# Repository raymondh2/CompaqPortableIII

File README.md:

# CompaqPortableIII

Current PCB Memory Expansion board layout is untested. The backplane for the expansion cards is tested and working.

Recreation of U10 Part Number 107393-001 working as expected so far. Recreation of U20 Part Number 107392-001 is untested.

The mainboard schematics are not verfied or complete.

## Other Projects
Replacement Battery Module by Sergey Kiselev [GitHub](https://github.com/skiselev/compaq-portable-iii-battery)

## License
This work is licensed under the CERN Open Hardware License v2 Strongly Reciprocal.
See [here](cern_ohl_s_v2_user_guide.txt).

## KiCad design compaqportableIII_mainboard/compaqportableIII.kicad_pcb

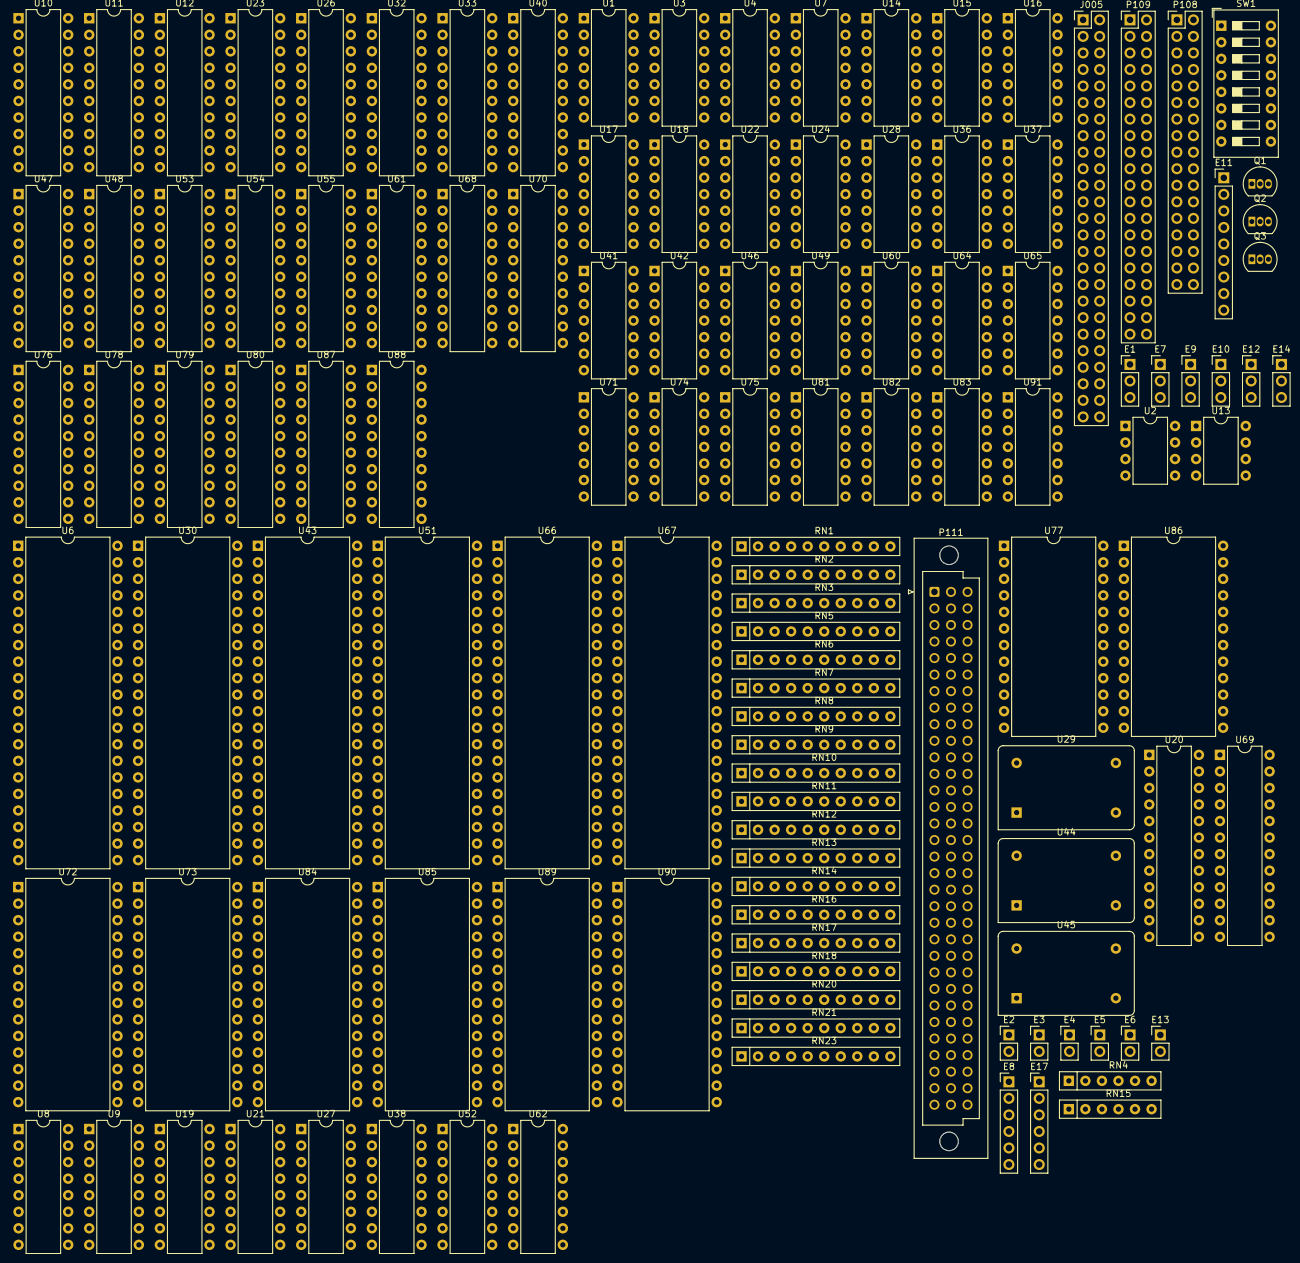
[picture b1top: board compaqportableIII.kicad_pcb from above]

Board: 2 copper layers, 123 parts (0 on the bottom side), 421 nets, no tracks yet.

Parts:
E1, E7, E9, E10, E12, E14: Conn_01x03; PinHeader_1x03_P2.54mm_Vertical
E2, E3, E4, E5, E6, E13: Conn_01x02; PinHeader_1x02_P2.54mm_Vertical
E8, E17: Conn_01x06; PinHeader_1x06_P2.54mm_Vertical
E11: Conn_01x09; PinHeader_1x09_P2.54mm_Vertical
J005: Conn_02x25_Odd_Even; PinHeader_2x25_P2.54mm_Vertical
P108: Conn_02x17_Odd_Even; PinHeader_2x17_P2.54mm_Vertical
P109: Conn_02x20_Odd_Even; PinHeader_2x20_P2.54mm_Vertical
P111: DIN41612_96abc; DIN41612_R_3x32_Male_Vertical_THT
Q1: TL431C; TO-92_Inline
Q2, Q3: PN2222A; TO-92_Inline
RN1: 1K; R_Array_SIP10
RN2: 2K; R_Array_SIP10
RN3, RN5, RN6, RN8, RN9, RN10, RN11, RN12, RN13, RN14, RN20, RN21, RN23: 8K2; R_Array_SIP10
RN4: 300R; R_Array_SIP6
RN7: 180; R_Array_SIP10
RN15: 100R; R_Array_SIP6
RN16, RN17, RN18: 33R; R_Array_SIP10
SW1: SW_DIP_x08; SW_DIP_SPSTx08_Slide_9.78x22.5mm_W7.62mm_P2.54mm
U1, U4: 7406N; DIP-14_W7.62mm
U2: SN75477; DIP-8_W7.62mm
U3: MC4024; DIP-14_W7.62mm
U6: D765; DIP-40_W15.24mm
U7: 74ALS00; DIP-14_W7.62mm
U8: 74LS112; DIP-16_W7.62mm
U9: MC3487N; DIP-16_W7.62mm
U10: PAL16L8; DIP-20_W7.62mm
U11, U23, U26: 74LS245; DIP-20_W7.62mm
U12: 74LS244; DIP-20_W7.62mm
U13: μA741CP; DIP-8_W7.62mm
U14: 74LS14; DIP-14_W7.62mm
U15: 74LS08; DIP-14_W7.62mm
U16, U91: 74ALS74; DIP-14_W7.62mm
U17: 74F08; DIP-14_W7.62mm
U18, U24, U37: 74LS125; DIP-14_W7.62mm
U19, U52: 74ALS138; DIP-16_W7.62mm
U20: PAL20L8; DIP-24_W7.62mm
U21, U27: MB8264A; DIP-16_W7.62mm
U22, U64: 74ALS04; DIP-14_W7.62mm
U28: 74LS05; DIP-14_W7.62mm
U29: F5C-S7; Oscillator_DIP-14
U30: 16450; DIP-40_W15.24mm
U32, U68, U78: 74F245; DIP-20_W7.62mm
U33, U48: 74ALS244; DIP-20_W7.62mm
U36, U41: 74F00; DIP-14_W7.62mm
U38, U62: 74LS367; DIP-16_W7.62mm
U40, U47, U70, U79, U80: 74ALS245; DIP-20_W7.62mm
U42: 74LS09; DIP-14_W7.62mm
U43: 80287; DIP-40_W15.24mm
U44: 1.843200 MHz; Oscillator_DIP-14
U45: 48 MHz; Oscillator_DIP-14
U46, U60: 74F32; DIP-14_W7.62mm
U49: 74F10; DIP-14_W7.62mm
U51: 8742; DIP-40_W15.24mm
U53: 74F257; DIP-20_W7.62mm
U54, U55, U61: 74F244; DIP-20_W7.62mm
U65: 74ALS27; DIP-14_W7.62mm
U66, U67: 8237; DIP-40_W15.24mm
U69: 74LS646; DIP-24_W7.62mm
U71, U81: 74LS280; DIP-14_W7.62mm
U72, U73, U89, U90: 27C256; DIP-28_W15.24mm
U74, U75: MC1489; DIP-14_W7.62mm
U76: 74LS374; DIP-20_W7.62mm
U77: MC146818A; DIP-24_W15.24mm
U82: MC1488; DIP-14_W7.62mm
U83: 4069; DIP-14_W7.62mm
U84, U85: 8259A-2; DIP-28_W15.24mm
U86: 8254; DIP-24_W15.24mm
U87, U88: 74LS373; DIP-20_W7.62mm

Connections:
+5V: E1.3, E10.1, E11.1, E11.4, E12.1, E13.1, E14.1, E17.1, E17.6, J005.1, J005.2, J005.49, J005.50, P111.a2 (Pin_c2), P111.a8 (Pin_c8), P111.c20, RN1.1 (R1), RN2.1 (R1), RN3.1 (common), RN4.1 (R1), RN5.1 (common), RN6.1 (common), RN8.1 (R1), RN9.1 (R1), RN10.1 (common), RN11.1 (R1), RN12.1 (common), RN13.1 (common), RN14.1 (common), RN20.1 (common), RN23.1 (common), U1.14 (VCC), U2.1 (S), U2.5 (Clamp), U2.8 (VCC), U6.35 (READY), U8.2 (K), U8.4 (~S), U8.10 (~S), U8.12 (K), U9.16 (VCC), U10.20 (VCC), U12.20 (VCC), U16.1 (~R), U16.10 (~S), U16.12 (D), U20.24 (VCC), U21.8 (VCC), U23.20 (VCC), U27.8 (VCC), U30.12 (CS0), U30.13 (CS1), U30.40 (VCC), U32.20 (VCC), U38.14 (I6), U38.16 (VCC), U43.9 (VCC), U43.39 (CKM), U47.20 (VCC), U48.20 (VCC), U51.25 (PROG), U51.26 (Vpp/VDD), U51.40 (VCC), U53.16 (VCC), U54.20 (VCC), U55.20 (VCC), U62.16 (VCC), U66.5 (PIN5), U66.31 (Vcc), U67.5 (PIN5), U67.31 (Vcc), U68.20 (VCC), U69.24 (VCC), U70.20 (VCC), U71.14 (VCC), U72.1 (VPP), U72.28 (VCC), U73.1 (VPP), U73.28 (VCC), U76.20 (VCC), U78.20 (VCC), U79.20 (VCC), U81.14 (VCC), U82.9, U82.13, U84.16 (~SP/~EN), U84.28 (VCC), U85.28 (VCC), U86.11 (G0), U86.14 (G1), U86.24 (VCC), U88.20 (VCC), U89.1 (VPP), U89.28 (VCC), U90.1 (VPP), U90.28 (VCC), U91.1 (~R), U91.4 (~S)
+12V: J005.47, P111.a6 (Pin_c6), P111.a20 (Pin_c20), U13.7 (V+)
+BATT: U77.24 (VCC), U83.14 (VDD)
-12V: J005.48, P111.b5 (Pin_c5), U13.4 (V-)
/AEN: J005.35, P111.a7 (Pin_c7), U33.16 (O1a)
/AEN2: U20.11 (I11), U33.4 (I1a), U64.2, U70.19 (CE)
/ALE: P111.b19 (Pin_c19), U33.14 (O2a)
/BA00: J005.11, P111.c21, RN20.2 (R1), U6.5 (A0), U12.13 (I1b), U20.10 (I10), U24.2, U24.6, U30.28 (A0)
/BA00_BUFF: U24.3, U24.5, U62.12 (I5), U69.22 (SBA)
/COM1: E3.1, U20.15 (IO15)
/COM2: E4.2, U20.18 (IO18)
/CPUB_A20: U47.5 (A3), U53.12 (Zc)
/CPUB_A21: U47.6 (A4), U53.9 (Zd)
/CPUB_A22: U47.7 (A5), U53.7 (Zb)
/CPUB_A23: U47.8 (A6), U53.4 (Za)
/CPU_A1: U62.4 (I2), U62.10 (I4)
/CPU_A2: U62.2 (I1), U62.6 (I3)
/CPU_A7: U37.9, U48.8 (I3a)
/CPU_A17: U33.15 (I2b), U47.2 (A0)
/CPU_A18: U33.13 (I1b), U47.3 (A1)
/CPU_A19: U33.17 (I3b), U47.4 (A2)
/CPU_A21: U53.10 (I1d), U53.11 (I0d)
/CPU_A22: U53.5 (I0b), U53.6 (I1b)
/CPU_A23: U53.2 (I0a), U53.3 (I1a)
/CPU_D0: U43.23 (D0), U69.11 (A8)
/CPU_D1: U43.22 (D1), U69.10 (A7)
/CPU_D2: U43.21 (D2), U69.9 (A6)
/CPU_D3: U43.20 (D3), U69.8 (A5)
/CPU_D4: U43.19 (D4), U69.7 (A4)
/CPU_D5: U43.18 (D5), U69.6 (A3)
/CPU_D6: U43.17 (D6), U69.5 (A2)
/CPU_D7: U43.16 (D7), U69.4 (A1)
/CPU_D8: U43.15 (D8), U79.9 (A7)
/CPU_D9: U43.14 (D9), U79.8 (A6)
/CPU_D10: U43.12 (D10), U79.7 (A5)
/CPU_D11: U43.11 (D11), U79.6 (A4)
/CPU_D12: U43.8 (D12), U79.5 (A3)
/CPU_D13: U43.7 (D13), U79.4 (A2)
/CPU_D14: U43.6 (D14), U79.3 (A1)
/CPU_D15: U43.5 (D15), U79.2 (A0)
/CPU_HDLA: U33.2 (I0a), U43.38 (HLDA), U53.15 (OE)
/CPU_~S0: RN6.3 (R2), U43.2 (~S0)
/CPU_~S1: RN6.4 (R3), U43.1 (~S1)
/Crystal_+5V: E13.2, U29.14 (VDD), U44.14 (VDD), U45.14 (VDD)
/DISKADD: E8.2, U20.23 (I23)
/DMA1_~CS: U19.15 (O0), U66.11 (~CS)
/DMA1_~EOP: U41.10, U66.36 (~EOP)
/DMA2_~CS: U19.9 (O6), U67.11 (~CS)
/DMA2_~EOP: U41.9, U67.36 (~EOP)
/DMA_CLK: RN7.6 (R3.2), U66.12 (CLK), U67.12 (CLK)
/DMA_RDY: U66.6 (READY), U67.6 (READY)
/DMA_RST: U33.8 (I3a), U33.11 (I0b), U64.11, U66.13 (RESET), U67.13 (RESET)
/DMA_~MEMR: RN11.7 (R6.2), U66.3 (~MEMR), U67.3 (~MEMR)
/DRQ0: P111.b27 (Pin_c27), RN21.2 (R1), U66.19 (DREQ0)
/DRQ1: P111.a12 (Pin_c12), RN21.3 (R2), U66.18 (DREQ1)
/DRQ2: P111.a4 (Pin_c4), RN21.4 (R3), U66.17 (DREQ2)
/DRQ3: P111.b11 (Pin_c11), RN21.5 (R4), U66.16 (DREQ3)
/DRQ5: P111.a28 (Pin_c28), RN21.7 (R6), U67.18 (DREQ1)
/DRQ6: P111.c30, RN21.8 (R7), U67.17 (DREQ2)
/DRQ7: P111.b31 (Pin_c31), RN21.9 (R8), U67.16 (DREQ3)
/DRQC: RN21.6 (R5), U66.10 (HRQ), U67.19 (DREQ0)
/DRVSB0: U1.1, U4.3
/DRVSB1: U1.5, U4.13
/DT/~R: U69.3 (DIR), U79.1 (A->B)
/EDB7: U18.3, U18.9, U18.11
/EXP_A1: J005.12, P111.b20 (Pin_c20), RN12.2 (R1), U12.15 (I2b), U20.9 (I9), U30.27 (A1), U40.2 (A0), U55.17 (I3b), U61.13 (I1b), U72.10 (A0), U73.10 (A0), U89.10 (A0), U90.10 (A0)
/EXP_A2: J005.13, P111.a19 (Pin_c19), RN12.3 (R2), U12.17 (I3b), U20.8 (I8), U30.26 (A2), U40.3 (A1), U55.15 (I2b), U61.11 (I0b), U72.9 (A1), U73.9 (A1), U89.9 (A1), U90.9 (A1)
/EXP_A3: J005.14, P111.c19, RN12.4 (R3), U20.7 (I7), U40.4 (A2), U55.13 (I1b), U72.8 (A2), U73.8 (A2), U89.8 (A2), U90.8 (A2)
/EXP_A4: J005.15, P111.b18 (Pin_c18), RN12.5 (R4), U20.6 (I6), U40.5 (A3), U55.11 (I0b), U72.7 (A3), U73.7 (A3), U89.7 (A3), U90.7 (A3)
/EXP_A5: J005.16, P111.a17 (Pin_c17), RN12.6 (R5), U19.1 (A0), U20.5 (I5), U40.6 (A4), U55.8 (I3a), U72.6 (A4), U73.6 (A4), U89.6 (A4), U90.6 (A4)
/EXP_A6: J005.17, P111.c17, RN12.7 (R6), U19.2 (A1), U20.4 (I4), U40.7 (A5), U55.6 (I2a), U72.5 (A5), U73.5 (A5), U89.5 (A5), U90.5 (A5)
/EXP_A7: J005.18, P111.b16 (Pin_c16), RN12.8 (R7), U19.3 (A2), U20.3 (I3), U40.8 (A6), U55.4 (I1a), U72.4 (A6), U73.4 (A6), U89.4 (A6), U90.4 (A6)
/EXP_A8: J005.19, P111.a15 (Pin_c15), RN12.9 (R8), U19.5 (E2), U20.2 (I2), U40.9 (A7), U55.2 (I0a), U72.3 (A7), U73.3 (A7), U89.3 (A7), U90.3 (A7)
/EXP_A9: J005.20, P111.c15, RN10.9 (R8), U19.4 (E1), U20.1 (I1), U54.17 (I3b), U61.17 (I3b), U62.13 (O6b), U72.25 (A8), U73.25 (A8), U87.5 (O1), U88.2 (O0), U89.25 (A8), U90.25 (A8)
/EXP_A10: J005.21, P111.b14 (Pin_c14), RN10.8 (R7), U54.15 (I2b), U61.15 (I2b), U72.24 (A9), U73.24 (A9), U87.19 (O7), U88.5 (O1), U89.24 (A9), U90.24 (A9)
/EXP_A11: J005.22, P111.a13 (Pin_c13), RN10.7 (R6), U54.13 (I1b), U72.21 (A10), U73.21 (A10), U87.16 (O6), U88.19 (O7), U89.21 (A10), U90.21 (A10)
/EXP_A12: J005.23, P111.c13, RN10.6 (R5), U54.11 (I0b), U72.23 (A11), U73.23 (A11), U87.6 (O2), U88.16 (O6), U89.23 (A11), U90.23 (A11)
/EXP_A13: J005.24, P111.b12 (Pin_c12), RN10.5 (R4), U54.8 (I3a), U72.2 (A12), U73.2 (A12), U87.9 (O3), U88.6 (O2), U89.2 (A12), U90.2 (A12)
/EXP_A14: E11.2, E11.3, J005.25, P111.a11 (Pin_c11), RN10.4 (R3), U38.6 (I3), U54.6 (I2a), U72.26 (A13), U73.26 (A13), U87.15 (O5), U88.9 (O3), U89.26 (A13), U90.26 (A13)
/EXP_A15: E10.3, E11.5, E11.6, J005.26, P111.c11, RN10.3 (R2), U38.4 (I2), U54.4 (I1a), U73.27 (A14), U87.12 (O4), U88.15 (O5), U90.27 (A14)
/EXP_A16: J005.27, P111.b10 (Pin_c10), RN10.2 (R1), U38.2 (I1), U54.2 (I0a), U88.12 (O4)
/EXP_A17: J005.28, P111.a9 (Pin_c9), RN23.2 (R1), U33.7 (O1b), U61.8 (I3a)
/EXP_A18: J005.29, P111.c9, RN12.10 (R9), U33.5 (O2b), U61.4 (I1a)
/EXP_A19: J005.30, P111.b8 (Pin_c8), RN10.10 (R9), U33.3 (O3b), U61.2 (I0a)
/EXP_LA17: P111.b26 (Pin_c26), U47.18 (B0)
/EXP_LA18: P111.a25 (Pin_c25), U47.17 (B1)
/EXP_LA20: P111.b24 (Pin_c24), U47.15 (B3)
/EXP_LA21: P111.a23 (Pin_c23), U47.14 (B4)
/EXP_LA22: P111.c25, U47.13 (B5)
/EXP_LA23: P111.b22 (Pin_c22), U47.12 (B6)
/EXP_RESET: P111.c2, U9.15 (INPUT), U33.12 (O3a)
/FDC_2SIDE: U6.34 (WPRT/2SIDE), U14.4
/FDC_DIR: U4.9, U6.38 (LCT/DIR)
/FDC_INDEX: U6.17 (INDEX), U14.2
/FDC_SEEK: U6.39 (m/SEEK), U15.9, U15.13
/FDC_SIDE: U4.5, U6.27 (SIDE)
/FDC_STEP: U6.37 (FLTR/STEP), U15.10
/FDC_TC: RN1.7 (R6.2), U6.16 (TC), U42.3
/FDC_TRK0: U6.33 (FLT/TRK0), U15.11
/FDC_WE: U6.25 (WE), U9.9 (INPUT)
/FDC_WINDOW: E2.1, U6.22 (WINDOW), U91.5 (Q)
/FLOPPYDACK: U6.15 (DACK), U10.12 (IO8)
/FPU_BUSY: RN11.2 (R1.2), U43.25 (BUSY)
/FPU_CLK: U43.32 (CLK), U43.37 (CLK286)
/FPU_~ERROR: RN9.10 (R9.2), U43.26 (~ERROR)
/FS_D0: RN3.2 (R1), U6.6 (DB0), U23.18 (B0), U30.1 (D0)
/FS_D1: RN3.3 (R2), U6.7 (DB1), U23.17 (B1), U30.2 (D1)
/FS_D2: RN3.4 (R3), U6.8 (DB2), U23.16 (B2), U30.3 (D2)
/FS_D3: RN3.5 (R4), U6.9 (DB3), U23.15 (B3), U30.4 (D3)
/FS_D4: RN3.6 (R5), U6.10 (DB4), U23.14 (B4), U30.5 (D4)
/FS_D5: RN3.7 (R6), U6.11 (DB5), U23.13 (B5), U30.6 (D5)
/FS_D6: RN3.8 (R7), U6.12 (DB6), U23.12 (B6), U30.7 (D6)
/FS_D7: RN3.9 (R8), U6.13 (DB7), U23.11 (B7), U30.8 (D7)
/H_QP: U21.14 (DOUT), U81.8 (A)
/IDE7_READ: U10.16 (IO4), U18.1
/IDE7_WRITE: U10.17 (I03), U18.10
/IDECS1: U12.11 (I0b), U20.19 (IO19)
/IDE_A0: P109.35, U12.7 (O1b)
/IDE_A1: P109.33, U12.5 (O2b)
/IDE_A2: P109.36, U12.3 (O3b)
/IDE_CSEL: P109.28, U12.12 (O3a)
/IDE_D0: P109.17, U11.11 (B7)
/IDE_D1: P109.15, U11.12 (B6)
/IDE_D2: P109.13, U11.13 (B5)
/IDE_D3: P109.11, U11.14 (B4)
/IDE_D4: P109.9, U11.15 (B3)
/IDE_D5: P109.7, U11.16 (B2)
/IDE_D6: P109.5, U11.17 (B1)
/IDE_D7: P109.3, U18.2, U18.8
/IDE_D8: P109.4, U26.18 (B0)
/IDE_D9: P109.6, U26.17 (B1)
/IDE_D10: P109.8, U26.16 (B2)
/IDE_D11: P109.10, U26.15 (B3)
/IDE_D12: P109.12, U26.14 (B4)
/IDE_D13: P109.14, U26.13 (B5)
/IDE_D14: P109.16, U26.12 (B6)
/IDE_D15: P109.18, U26.11 (B7)
/IDE_INTRQ: P109.31, P111.c26, U85.24 (IR6)
/IDE_~ACTIVE: P109.39, U4.12
/IDE_~CS0: P109.37, U10.11 (I10), U20.20 (I020)
/IDE_~CS1: P109.38, U12.9 (O0b)
/IDE_~DIOR: P109.25, U12.16 (O1a)
/IDE_~DIOW: P109.23, U12.18 (O0a)
/IDE_~RESET: P109.1, U12.14 (O2a)
/IO_READY: P111.c7, U42.6
/IRQ0: U84.18 (IR0), U86.10 (OUT0)
/IRQ1: U51.35 (P24/OBF), U65.10, U84.19 (IR1)
/IRQ2: U65.1, U84.20 (IR2), U85.17 (INT)
/IRQ3: E5.1, P111.b17 (Pin_c17), U84.21 (IR3)
/IRQ4: E6.2, P111.a16 (Pin_c16), U84.22 (IR4)
/IRQ5: P111.c16, U84.23 (IR5)
/IRQ6: P111.b15 (Pin_c15), U9.2 (OUT+), U84.24 (IR6)
/IRQ7: P111.a14 (Pin_c14), U84.25 (IR7)
/IRQ8_RTC: U64.8, U85.18 (IR0)
/IRQ9: J005.36, P111.b3 (Pin_c3), U85.19 (IR1)
/IRQ10: P111.b23 (Pin_c23), U85.20 (IR2)
/IRQ11: P111.c24, U85.21 (IR3)
/IRQ12: P111.a24 (Pin_c24), U85.22 (IR4)
/IRQ15: P111.b25 (Pin_c25), U85.25 (IR7)
/IRQ_CAS0: U84.12 (CAS0), U85.12 (CAS0)
/IRQ_CAS1: U84.13 (CAS1), U85.13 (CAS1)
/IRQ_CAS2: U84.15 (CAS2), U85.15 (CAS2)
/IRQ_~INTA: U84.26 (~INTA), U85.26 (~INTA)
/KBC_~RESET: J005.46, RN11.9 (R8.2), U16.4 (~S), U51.4 (~RESET), U64.10
/KBC_~WR: RN11.8 (R7.2), U51.10 (~WR)
/LPT_~AUTOFD: RN2.4 (R3.2), U28.4
/LPT_~INIT: RN2.2 (R1.2), U28.10
/LPT_~SELIN: RN2.5 (R4.2), U28.12
/LPT_~STROBE: RN2.3 (R2.2), U28.2
/MASTER: P111.b32 (Pin_c32), RN4.6 (R5.2), U32.1 (A->B), U41.4, U41.13, U47.1 (A->B), U49.9
/MEMBUFF2_A6: E9.1, E9.2, U21.13 (A6), U27.13 (A6), U37.3, U37.6, U37.8, U37.11
/MEMBUFF_A1: RN17.10 (R5.2), U21.5 (A0), U27.5 (A0)
/MEMBUFF_A2: RN17.8 (R4.2), U21.7 (A1), U27.7 (A1)
/MEMBUFF_A3: RN17.6 (R3.2), U21.6 (A2), U27.6 (A2)
/MEMBUFF_A4: RN17.4 (R2.2), U21.12 (A3), U27.12 (A3)
/MEMBUFF_A5: RN17.2 (R1.2), U21.11 (A4), U27.11 (A4)
/MEMBUFF_A6: RN16.10 (R5.2), U21.10 (A5), U27.10 (A5)
/MEMBUFF_A7: E9.3, RN16.8 (R4.2)
/MEMBUFF_A8: RN16.6 (R3.2), U21.9 (A7), U27.9 (A7)
/MEMBUFF_CASH: RN18.6 (R3.2), U21.15 (~CAS)
/MEMBUFF_CASL: RN18.8 (R4.2), U27.15 (~CAS)
/MEMBUFF_~RAS: RN18.2 (R1.2), U21.4 (~RAS), U27.4 (~RAS)
/MEME_A2: U61.9 (O0b), U61.18 (O0a), U62.7 (O3a)
/MEM_A1: RN17.9 (R5.1), U54.3 (O3b), U55.3 (O3b), U62.5 (O2a)
/MEM_A2: RN17.7 (R4.1), U54.5 (O2b), U55.5 (O2b), U62.3 (O1a)
/MEM_A3: RN17.5 (R3.1), U48.3 (O3b), U54.7 (O1b), U55.7 (O1b)
/MEM_A4: RN17.3 (R2.1), U48.5 (O2b), U54.9 (O0b), U55.9 (O0b)
/MEM_A5: RN17.1 (R1.1), U48.7 (O1b), U54.12 (O3a), U55.12 (O3a)
/MEM_A6: RN16.9 (R5.1), U48.9 (O0b), U54.14 (O2a), U55.14 (O2a)
/MEM_A7: RN16.7 (R4.1), U48.12 (O3a), U54.16 (O1a), U55.16 (O1a)
/MEM_A8: RN16.5 (R3.1), U48.14 (O2a), U54.18 (O0a), U55.18 (O0a)
/MEM_A9: RN16.3 (R2.1), U48.16 (O1a), U61.3 (O3b), U61.12 (O3a)
/MEM_A10: RN16.1 (R1.1), U48.18 (O0a), U61.5 (O2b), U61.14 (O2a)
/MEM_D0: RN13.2 (R1), U68.11 (B7), U89.11 (D0), U90.11 (D0)
/MEM_D1: RN13.3 (R2), U68.12 (B6), U89.12 (D1), U90.12 (D1)
/MEM_D2: RN13.4 (R3), U68.13 (B5), U89.13 (D2), U90.13 (D2)
/MEM_D3: RN13.5 (R4), U68.14 (B4), U89.15 (D3), U90.15 (D3)
/MEM_D4: RN13.6 (R5), U68.15 (B3), U89.16 (D4), U90.16 (D4)
/MEM_D5: RN13.7 (R6), U68.16 (B2), U89.17 (D5), U90.17 (D5)
/MEM_D6: RN13.8 (R7), U68.17 (B1), U89.18 (D6), U90.18 (D6)
/MEM_D7: RN13.9 (R8), U68.18 (B0), U89.19 (D7), U90.19 (D7)
/MEM_D8: RN14.2 (R1), U72.11 (D0), U73.11 (D0), U78.11 (B7)
/MEM_D9: RN14.3 (R2), U72.12 (D1), U73.12 (D1), U78.12 (B6)
/MEM_D10: RN14.4 (R3), U72.13 (D2), U73.13 (D2), U78.13 (B5)
/MEM_D11: RN14.5 (R4), U72.15 (D3), U73.15 (D3), U78.14 (B4)
/MEM_D12: RN14.6 (R5), U72.16 (D4), U73.16 (D4), U78.15 (B3)
/MEM_D13: RN14.7 (R6), U72.17 (D5), U73.17 (D5), U78.16 (B2)
/MEM_D14: RN14.8 (R7), U72.18 (D6), U73.18 (D6), U78.17 (B1)
/MEM_D15: RN14.9 (R8), U72.19 (D7), U73.19 (D7), U78.18 (B0)
/MEM_~W: U21.3 (~WE), U27.3 (~WE)
/MODEM_IRQ: E6.1, U65.13
/OBUARTCS2: E3.2, U10.9 (I9), U30.14 (~CS2)
/OWS_N: P111.c6, RN4.2 (R1.2)
/P107_P7: RN6.9 (R8), RN6.10 (R9), U42.8, U51.1 (T0)
/P107_P8: RN6.7 (R6), RN6.8 (R7), U42.11, U51.39 (T1)
/PIC1_~CS: U19.14 (O1), U84.1 (~CS)
/PIC2_~CS: U19.10 (O5), U85.1 (~CS)
/PIT_~CS: U19.13 (O2), U86.21 (~CS)
/PRINTER: E7.2, U20.22 (IO22)
/SBHE: P111.a21 (Pin_c21), RN8.4 (R3.2), U32.12 (B6)
/STEP: U4.11, U15.8
/SW1_DIP1: RN5.2 (R1), SW1.1
/SW1_DIP2: RN5.3 (R2), SW1.2
/SW1_DIP3: RN5.4 (R3), SW1.3
/SW1_DIP4: RN5.5 (R4), SW1.4
/SW1_DIP5: RN5.6 (R5), SW1.5, U10.6 (I6)
/SW1_DIP6: RN5.7 (R6), SW1.6, U51.31 (P14)
/SW1_DIP7: RN5.8 (R7), SW1.7, U51.33 (P16)
/SW1_DIP8: RN5.9 (R8), SW1.8, U51.32 (P15)
/SYS2_A0: U37.2, U66.32 (A0), U84.27 (A0), U85.27 (A0), U86.19 (A0)
/SYS2_A1: U40.18 (B0), U66.33 (A1), U67.32 (A0), U86.20 (A1)
/SYS2_A2: U40.17 (B1), U51.9 (A0), U66.34 (A2), U67.33 (A1)
/SYS2_A3: U40.16 (B2), U66.35 (A3), U67.34 (A2)
/SYS2_A4: U40.15 (B3), U66.37 (A4), U67.35 (A3)
/SYS2_A5: U40.14 (B4), U66.38 (A5), U67.37 (A4)
/SYS2_A6: U40.13 (B5), U66.39 (A6), U67.38 (A5)
/SYS2_A7: U40.12 (B6), U66.40 (A7), U67.39 (A6)
/SYS2_A8: U40.11 (B7), U67.40 (A7)
/SYS2_D0: U51.12 (D0), U66.21 (DB7), U67.21 (DB7), U70.11 (B7), U76.3 (D0), U77.4 (AD0), U84.4 (D7), U85.4 (D7), U86.8 (D0), U87.3 (D0), U88.3 (D0)
/SYS2_D1: U51.13 (D1), U66.22 (DB6), U67.22 (DB6), U70.12 (B6), U76.4 (D1), U77.5 (AD1), U84.5 (D6), U85.5 (D6), U86.7 (D1), U87.4 (D1), U88.4 (D1)
/SYS2_D2: U51.14 (D2), U66.23 (DB5), U67.23 (DB5), U70.13 (B5), U76.7 (D2), U77.6 (AD2), U84.6 (D5), U85.6 (D5), U86.6 (D2), U87.18 (D7), U88.18 (D7)
/SYS2_D3: U51.15 (D3), U66.26 (DB4), U67.26 (DB4), U70.14 (B4), U76.8 (D3), U77.7 (AD3), U84.7 (D4), U85.7 (D4), U86.5 (D3), U87.17 (D6), U88.17 (D6)
/SYS2_D4: U51.16 (D4), U66.27 (DB3), U67.27 (DB3), U70.15 (B3), U76.13 (D4), U77.8 (AD4), U84.8 (D3), U85.8 (D3), U86.4 (D4), U87.7 (D2), U88.7 (D2)
/SYS2_D5: U51.17 (D5), U66.28 (DB2), U67.28 (DB2), U70.16 (B2), U76.14 (D5), U77.9 (AD5), U84.9 (D2), U85.9 (D2), U86.3 (D5), U87.8 (D3), U88.8 (D3)
/SYS2_D6: U51.18 (D6), U66.29 (DB1), U67.29 (DB1), U70.17 (B1), U76.17 (D6), U77.10 (AD6), U84.10 (D1), U85.10 (D1), U86.2 (D6), U87.14 (D5), U88.14 (D5)
/SYS2_D7: U51.19 (D7), U66.30 (DB0), U67.30 (DB0), U70.18 (B0), U76.18 (D7), U77.11 (AD7), U84.11 (D0), U85.11 (D0), U86.1 (D7), U87.13 (D4), U88.13 (D4)
/SYS2_~RD: U51.8 (~RD), U66.1 (~IOR), U67.1 (~IOR), U84.3 (~RD), U85.3 (~RD), U86.22 (~RD)
/SYSCLK: P111.c14, RN7.4 (R2.2)
/SYSIOR: U6.2 (RD), U10.4 (I4), U11.1 (A->B), U12.4 (I1a), U14.11, U23.1 (A->B), U26.1 (A->B), U32.6 (A4), U43.27 (~NPRD)
/SYSROM_A15: E10.2, U72.27 (A14), U89.27 (A14)
/SYS_D0: J005.3, P111.b6 (Pin_c6), RN20.10 (R9), U11.9 (A7), U23.9 (A7), U68.9 (A7), U69.13 (B8), U70.9 (A7), U71.9 (B), U80.9 (A7)
/SYS_D1: J005.4, P111.a5 (Pin_c5), RN20.9 (R8), U11.8 (A6), U23.8 (A6), U68.8 (A6), U69.14 (B7), U70.8 (A6), U71.10 (C), U80.8 (A6)
/SYS_D2: J005.5, P111.c5, RN20.8 (R7), U11.7 (A5), U23.7 (A5), U68.7 (A5), U69.15 (B6), U70.7 (A5), U71.4 (I), U80.7 (A5)
/SYS_D3: J005.6, P111.b4 (Pin_c4), RN20.7 (R6), U11.6 (A4), U23.6 (A4), U68.6 (A4), U69.16 (B5), U70.6 (A4), U71.11 (D), U80.6 (A4)
/SYS_D4: J005.7, P111.a3 (Pin_c3), RN20.6 (R5), U11.5 (A3), U20.13 (I13), U23.5 (A3), U68.5 (A3), U69.17 (B4), U70.5 (A3), U71.12 (E), U80.5 (A3)
/SYS_D5: J005.8, P111.c3, RN20.5 (R4), U11.4 (A2), U23.4 (A2), U68.4 (A2), U69.18 (B3), U70.4 (A2), U71.2 (H), U80.4 (A2)
/SYS_D6: J005.9, P111.b2 (Pin_c2), RN20.4 (R3), U11.3 (A1), U23.3 (A1), U68.3 (A1), U69.19 (B2), U70.3 (A1), U71.13 (F), U80.3 (A1)
/SYS_D7: J005.10, P111.a1 (Pin_c1), RN20.3 (R2), U23.2 (A0), U68.2 (A0), U69.20 (B1), U70.2 (A0), U71.1 (G), U80.2 (A0)
/SYS_D8: P111.b28 (Pin_c28), RN23.10 (R9), U26.2 (A0), U78.9 (A7), U79.11 (B7), U80.11 (B7), U81.9 (B)
/SYS_D9: P111.c29, RN23.9 (R8), U26.3 (A1), U78.8 (A6), U79.12 (B6), U80.12 (B6), U81.10 (C)
/SYS_D10: P111.a29 (Pin_c29), RN23.8 (R7), U26.4 (A2), U78.7 (A5), U79.13 (B5), U80.13 (B5), U81.4 (I)
/SYS_D11: P111.b30 (Pin_c30), RN23.7 (R6), U26.5 (A3), U78.6 (A4), U79.14 (B4), U80.14 (B4), U81.11 (D)
/SYS_D12: P111.c31, RN23.6 (R5), U26.6 (A4), U78.5 (A3), U79.15 (B3), U80.15 (B3), U81.12 (E)
/SYS_D13: P111.a31 (Pin_c31), RN23.5 (R4), U26.7 (A5), U78.4 (A2), U79.16 (B2), U80.16 (B2), U81.2 (H)
/SYS_D14: P111.c32, RN23.4 (R3), U26.8 (A6), U78.3 (A1), U79.17 (B1), U80.17 (B1), U81.13 (F)
/SYS_D15: P111.a32 (Pin_c32), RN23.3 (R2), U26.9 (A7), U78.2 (A0), U79.18 (B0), U80.18 (B0), U81.1 (G)
/SYS_IOW: U12.2 (I0a), U20.14 (I14), U30.18 (~WR), U32.7 (A5), U43.28 (~NPWR), U66.2 (~IOW), U67.2 (~IOW), U84.2 (~WR), U85.2 (~WR), U86.23 (~WR)
/TC: P111.a18 (Pin_c18), U41.8, U42.2
/U2_P2: U2.2 (1A), U2.7 (2A)
/U5_P1: U10.8 (I8), U18.13
/U5_P14: U9.12 (ENABLE), U9.14 (OUT+), U30.35 (MR)
/U5_P60: U8.3 (J), U8.13 (C), U8.15 (~R), U91.3 (C)
/U5_P62: U8.1 (C), U8.11 (J), U8.14 (~R)
/U7_P2: U7.2, U16.11 (C)
/U7_P4: U7.4, U16.3 (C)
/U9_P4: U9.4 (ENABLE), U10.3 (I3)
/U10_P7: U10.7 (I7), U20.21 (IO21)
/U10_P13: U10.13 (IO7), U20.17 (IO17)
/U10_P15: U10.15 (IO5), U23.19 (CE)
/U10_P18: U10.18 (IO2), U26.19 (CE)
/U10_P19: U10.19 (IO1), U11.19 (CE)
/U12_P8: U12.8 (I3a), U33.6 (I2a)
/U16_P9: U16.9 (Q), U69.21 (~G)
/U17_P3: U17.3, U60.9
/U17_P9: RN9.5 (R4.2), U17.9, U17.10, U32.5 (A3), U41.2, U66.4 (~MEMW), U67.4 (~MEMW)
/U17_P12: U17.12, U36.2, U36.5
/U18_P6: E5.2, U18.6, U65.2
/U19_P6: U19.6 (E3), U33.19 (OEb), U41.11, U64.1
/U22_P8: RN9.8 (R7.2), U32.8 (A6)
/U22_P9: RN2.10 (R9.2), U22.9, U32.9 (A7), U37.1, U62.15 (OEb)
/U27_DOUT: U27.14 (DOUT), U71.8 (A)
/U31_P37: RN9.3 (R2.2), U38.15 (OEb)
/U31_P45: RN9.4 (R3.2), U68.1 (A->B), U78.1 (A->B)
/U32_P4: U32.4 (A2), U41.1
/U33_P18: U33.18 (O0a), U41.12, U46.5, U64.13
/U34_P14: U38.9 (O4a), U61.6 (I2a)
/U35_P1: U49.1, U49.4
/U35_P12: U46.2, U46.4
/U37_P13: U37.13, U54.1 (OEa), U54.19 (OEb), U61.1 (OEa)
/U42_P17: J005.45, U42.4, U42.5
/U46+P3: U46.3, U55.1 (OEa), U55.19 (OEb), U60.12, U61.19 (OEb)
/U46_P6: U37.10, U46.6, U48.1 (OEa), U48.19 (OEb), U62.1 (OEa)
/U49_P13: U49.3, U49.13
/U50_P35: RN7.10 (R5.2), U51.3 (X2)
/U56_P31: U17.1, U60.2
/U56_P42: U17.2, U60.5
/U56_P49: E11.8, E11.9, E12.3, U73.20 (~CE), U73.22 (~OE), U90.20 (~CE), U90.22 (~OE)
/U56_P52: E11.7, U36.12, U72.20 (~CE), U89.20 (~CE)
/U56_P53: U72.22 (~OE), U89.22 (~OE)
/U56_P57: J005.32, P111.c8, U36.13
/U60_P3: U60.3, U78.19 (CE)
/U60_P6: U60.6, U68.19 (CE)
/U62_P11: U62.11 (O5b), U87.2 (O0)
/U64_P12: U38.1 (OEa), U46.1, U64.12
/U66_ADSTB: U66.8 (ADSTB), U87.11 (LE)
/U66_AEN: U41.5, U66.9 (AEN)
/U67_ADSTB: U67.8 (ADSTB), U88.11 (LE)
/U67_AEN: U49.11, U67.9 (AEN)
/U67_DACK0: U49.10, U64.3, U67.25 (DACK0)
/U87_OE: U41.6, U87.1 (OE)
/U88_OE: U49.8, U88.1 (OE)
/UART_SIN: U30.10 (SIN), U75.11
/UART_SOUT: U30.11 (SOUT), U82.2
/UART_~CTS: U30.36 (~CTS), U74.8
/UART_~DCD: U30.38 (~DCD), U74.3
/UART_~DSR: U30.37 (~DSR), U74.6
/UART_~DTR: U30.33 (~DTR), U82.12
/UART_~RI: U30.39 (~RI), U74.11
/UART_~RTS: U30.32 (~RTS), U82.10
/VCC_VCM: U3.1 (VCC), U3.14 (BUFF_VCC)
/disk: E8.5, U20.16 (IO16)
/~DACK0: P111.a26 (Pin_c26), U66.25 (DACK0)
/~DACK1: P111.c12, U66.24 (DACK1)
/~DACK2: P111.c18, U10.2 (I2), U22.1, U66.14 (DACK2)
/~DACK3: P111.a10 (Pin_c10), U66.15 (DACK3)
/~DACK5: P111.c28, U67.24 (DACK1)
/~DACK6: P111.b29 (Pin_c29), U67.14 (DACK2)
/~DACK7: P111.a30 (Pin_c30), U67.15 (DACK3)
/~DIR: P108.18, U4.8
/~DRVSB0: P108.14, U1.2
/~DRVSB1: P108.12, U1.6
/~DSKCHG: P108.34, RN1.5 (R4.2), U14.9
/~INDEX: P108.8, RN1.2 (R1.2), U14.1
/~IOCS16: P109.32, P111.a22 (Pin_c22), RN4.5 (R4.2), U10.5 (I5), U22.5
/~IOR: J005.41, P111.c10, RN8.3 (R2.2), U32.14 (B4)
/~IOW: P111.b9 (Pin_c9), RN8.2 (R1.2), U32.13 (B5), U46.9
/~MEMCS16: P111.c22, RN4.4 (R3.2), U24.11, U38.11 (O5b)
/~MEMR: J005.37, P111.c27, RN8.5 (R4.2), U32.16 (B2)
/~MEMW: J005.39, P111.a27 (Pin_c27), RN8.6 (R5.2), U32.15 (B3)
/~MOTEA: P108.10, U1.4
/~MOTEB: P108.16, U1.8
/~RDATA: P108.30, RN1.6 (R5.2)
/~REDWC: P108.2, U1.12
/~REFRESH: J005.33, P111.b13 (Pin_c13), RN4.3 (R2.2), U32.11 (B7)
/~ReserverdFDC6: P108.6, U1.10
/~SIDE1: P108.32, U4.6
/~STEP: P108.20, U4.10
/~TRACK00: P108.26, RN1.4 (R3.2), U14.5
/~WDATA: P108.22, U4.2
/~WGATE: P108.24, U9.11 (OUT-)
/~WPT: P108.28, RN1.3 (R2.2), U14.3
GND: E8.3, E8.6, E14.2, E14.3, E17.3, E17.4, J005.34, J005.38, J005.40, J005.42, J005.44, P108.1, P108.3, P108.5, P108.7, P108.9, P108.11, P108.13, P108.15, P108.17, P108.19, P108.21, P108.23, P108.25, P108.27, P108.29, P108.31, P108.33, P109.2, P109.19, P109.22, P109.24, P109.26, P109.30, P109.40, P111.b1 (Pin_c1), P111.b7 (Pin_c7), P111.b21 (Pin_c21), P111.c4, Q1.2 (A), Q2.1 (E), RN15.1 (R1), RN21.1 (common), SW1.9, SW1.10, SW1.11, SW1.12, SW1.13, SW1.14, SW1.15, SW1.16, U1.7 (GND), U2.4 (GND), U3.5 (GND), U3.7 (GND), U3.9 (GND), U9.8 (GND), U10.10 (GND), U12.10 (GND), U16.2 (D), U20.12 (GND), U21.16 (GND), U23.10 (GND), U24.12, U27.16 (GND), U29.7 (GND), U30.19 (WR), U30.20 (GND), U30.22 (RD), U30.25 (~ADS), U32.10 (GND), U38.8 (GND), U38.12 (I5), U40.10 (GND), U43.10 (GND), U43.29 (CMD0), U43.30 (GND), U43.31 (CMD1), U44.7 (GND), U45.7 (GND), U47.10 (GND), U48.10 (GND), U51.2 (X1), U51.20 (GND), U51.28 (P11), U53.14 (I0c), U66.20 (Vss), U67.20 (Vss), U69.1 (CAB), U69.2 (SAB), U70.10 (GND), U71.7 (GND), U72.14 (GND), U73.14 (GND), U76.1 (OE), U76.10 (GND), U77.1 (MOT), U77.12 (GND), U77.20 (CKFS), U81.7 (GND), U82.7 (GND), U83.7 (VSS), U84.14 (GND), U85.14 (GND), U85.16 (~SP/~EN), U86.12 (GND), U87.10 (GND), U88.10 (GND), U89.14 (GND), U90.14 (GND)
unnamed: E1.2, U15.4
unnamed: E8.1, RN11.3 (R2.2)
unnamed: E8.4, RN11.4 (R3.2)
unnamed: E12.2, U17.4
unnamed: J005.31, U65.8
unnamed: J005.43, U46.8
unnamed: Q3.3 (C), U13.2 (-)
unnamed: U83.2, U83.13
unnamed: RN2.6 (R5.2), U8.5 (Q)
unnamed: RN2.7 (R6.2), U8.9 (Q)
unnamed: RN7.8 (R4.2), U86.9 (CLK0), U86.15 (CLK1), U86.18 (CLK2)
unnamed: RN11.5 (R4.2), U30.16 (XIN), U44.8 (OUT)
unnamed: RN15.2 (R1.2), U40.19 (CE)
unnamed: RN15.3 (R2.2), U33.1 (OEa)
unnamed: RN15.4 (R3.2), U47.19 (CE)
unnamed: RN18.1 (R1.1), U49.12
unnamed: RN18.3 (R2.1), U49.6
unnamed: RN18.5 (R3.1), U36.3
unnamed: RN18.7 (R4.1), U36.6, U60.10
unnamed: RN18.9 (R5.1), U61.7 (O1b), U61.16 (O1a), U62.9 (O4a)
unnamed: U6.18 (INT), U9.1 (INPUT)
unnamed: U7.1, U7.6, U7.9
unnamed: U7.3, U7.5
unnamed: U11.2 (A0), U11.18 (B0)
unnamed: U9.13 (OUT-), U12.6 (I2a)
unnamed: U12.1 (OEa), U12.19 (OEb)
unnamed: U14.6, U15.12
unnamed: U14.8, U18.12
unnamed: U14.10, U14.13
unnamed: U7.10, U16.6 (~Q)
unnamed: U17.6, U22.13
unnamed: U17.5, U17.11, U36.10, U36.11
unnamed: U22.2, U42.1
unnamed: U22.6, U46.10
unnamed: U22.8, U60.13
unnamed: U22.12, U60.1, U60.4
unnamed: U18.5, U30.30 (INTR)
unnamed: U30.9 (RCLK), U30.15 (~BAUDOUT)
unnamed: U18.4, U30.31 (~OUT2)
unnamed: U14.12, U30.21 (~RD)
unnamed: U32.2 (A0), U32.18 (B0)
unnamed: U32.3 (A1), U32.17 (B1)
unnamed: U37.4, U60.11
unnamed: U42.9, U42.10, U64.6
unnamed: U47.9 (A7), U47.11 (B7)
unnamed: U15.5, U51.23 (P22)
unnamed: U51.37 (P26/DRQ), U64.5
unnamed: U42.12, U42.13, U51.38 (P27/~DACK)
unnamed: U65.6, U65.11
unnamed: U65.3, U65.4, U65.5, U65.12
unnamed: U64.4, U66.7 (HLDA)
unnamed: U77.2 (OSC1), U83.10
unnamed: U77.18 (~RESET), U77.22 (PS)
unnamed: U77.13 (~CS), U83.8
unnamed: U64.9, U77.19 (~IRQ)
unnamed: U77.16 (~STBY), U83.6, U83.9
unnamed: U83.4, U83.5
unnamed: U83.11, U83.12
unnamed: U91.2 (D), U91.6 (~Q)

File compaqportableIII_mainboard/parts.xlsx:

U1 | 7406N |  |  | P
U2 | SN75477P |  |  | P
U3 | MC4024P |  |  | P
U4 | SN7406N |  |  | P
U5 | Custom
U6 | D765AC-2 |  |  | P
U7 | 74ALS00 |  |  | P
U8 | 74LS112AN |  |  | P
U9 | MC3487P |  |  | P
U10 | AMPAL16L8APC | 107393-001 |  | P
U11 | 74LS245 |  |  | P
U12 | 74LS244 |  |  | P
U13 | UA741CP |  |  | P
U14 | 74LS14N |  |  | P
U15 | 74LS08N |  |  | P
U16 | 74ALS74AN |  |  | P
U17 | 74F08 |  |  | P
U18 | 74LS125A |  |  | P
U19 | 74ALS138 |  |  | P
U20 | PAL20L8ACNS | 107392-001 |  | P
U21 | MB8264A-10 |  |  | P
U22 | 74ALS04BN |  |  | P
U23 | 74LS245 |  |  | P
U24 | 74LS125A |  |  | P
U25 | 74ALS573 |  |  | P
U26 | 74LS245 |  |  | P
U27 | MB8264A-10 |  |  | P
U28 | 74LS05 |  |  | P
U29 | F5C-S7 | 14.31818 | 24
U30 | NS16450N |  |  | P
U31 | MB672322 | 104473-004
U32 | 74F245 |  |  | P
U33 | 74ALS244 |  |  | P
U34 | 74ALS573 |  |  | P
U35 |  | Delay line?
U36 | 74F00 |  |  | P
U37 | 74LS125A |  |  | P
U38 | 74LS367 |  |  | P
U39 | 74ALS573 |  |  | P
U40 | 74ALS245 |  |  | P
U41 | 74F00 |  |  | P
U42 | 74LS09 |  |  | P
U43 | i80287 |  |  | P
U44 | 970T | 1.8432 MHz
U45 | NCT070C | 48 MHz
U46 | 74F32 |  |  | P
U47 | 74ALS245 |  |  | P
U48 | 74ALS244 |  |  | P
U49 | 74F10 |  |  | P
U50 | MB672316U | 104474-001
U51 | D8742 | 106436-002 |  | P
U52 | i80286
U53 | 74F257 |  |  | P
U54 | 74F244 |  |  | P
U55 | 74F244 |  |  | P
U56 | MB672318 | 104475-002
U57 | TMS4464-10NL |  |  | P
U58 | TMS4464-10NL |  |  | P
U59 | TMS4464-10NL |  |  | P
U60 | 74F32 |  |  | P
U61 | 74F244 |  |  | P
U62 | 74LS367 |  |  | P
U63 | TMS4464-10NL |  |  | P
U64 | 74ALS04BN |  |  | P
U65 | 74ALS27 |  |  | P
U66 | D8237AC-5 |  |  | P
U67 | D8237AC-5 |  |  | P
U68 | 74F245 |  |  | P
U69 | 74AS646 |  |  | P
U70 | 74ALS245 |  |  | P
U71 | 74F280 |  |  | P
U72 | ROM
U73 | ROM
U74 | MC1489A | SN75189 |  | P
U75 | MC1489AP |  |  | P
U76 | 74LS374N |  |  | P
U77 | MC146818P
U78 | 74F245 |  |  | P
U79 | 74ALS245 |  |  | P
U80 | 74ALS245 |  |  | P
U81 | 74F280 |  |  | P
U82 | MC1488 | 75188N |  | P
U83 | MC14069UBCP
U84 | SAB8259A2P |  |  | P
U85 | SAB8259A2P |  |  | P
U86 | P8254 |  |  | P
U87 | 74LS373 |  |  | P
U88 | 74LS373 |  |  | P
U89 | ROM
U90 | ROM
U91 | 74ALS74AN |  |  | P
